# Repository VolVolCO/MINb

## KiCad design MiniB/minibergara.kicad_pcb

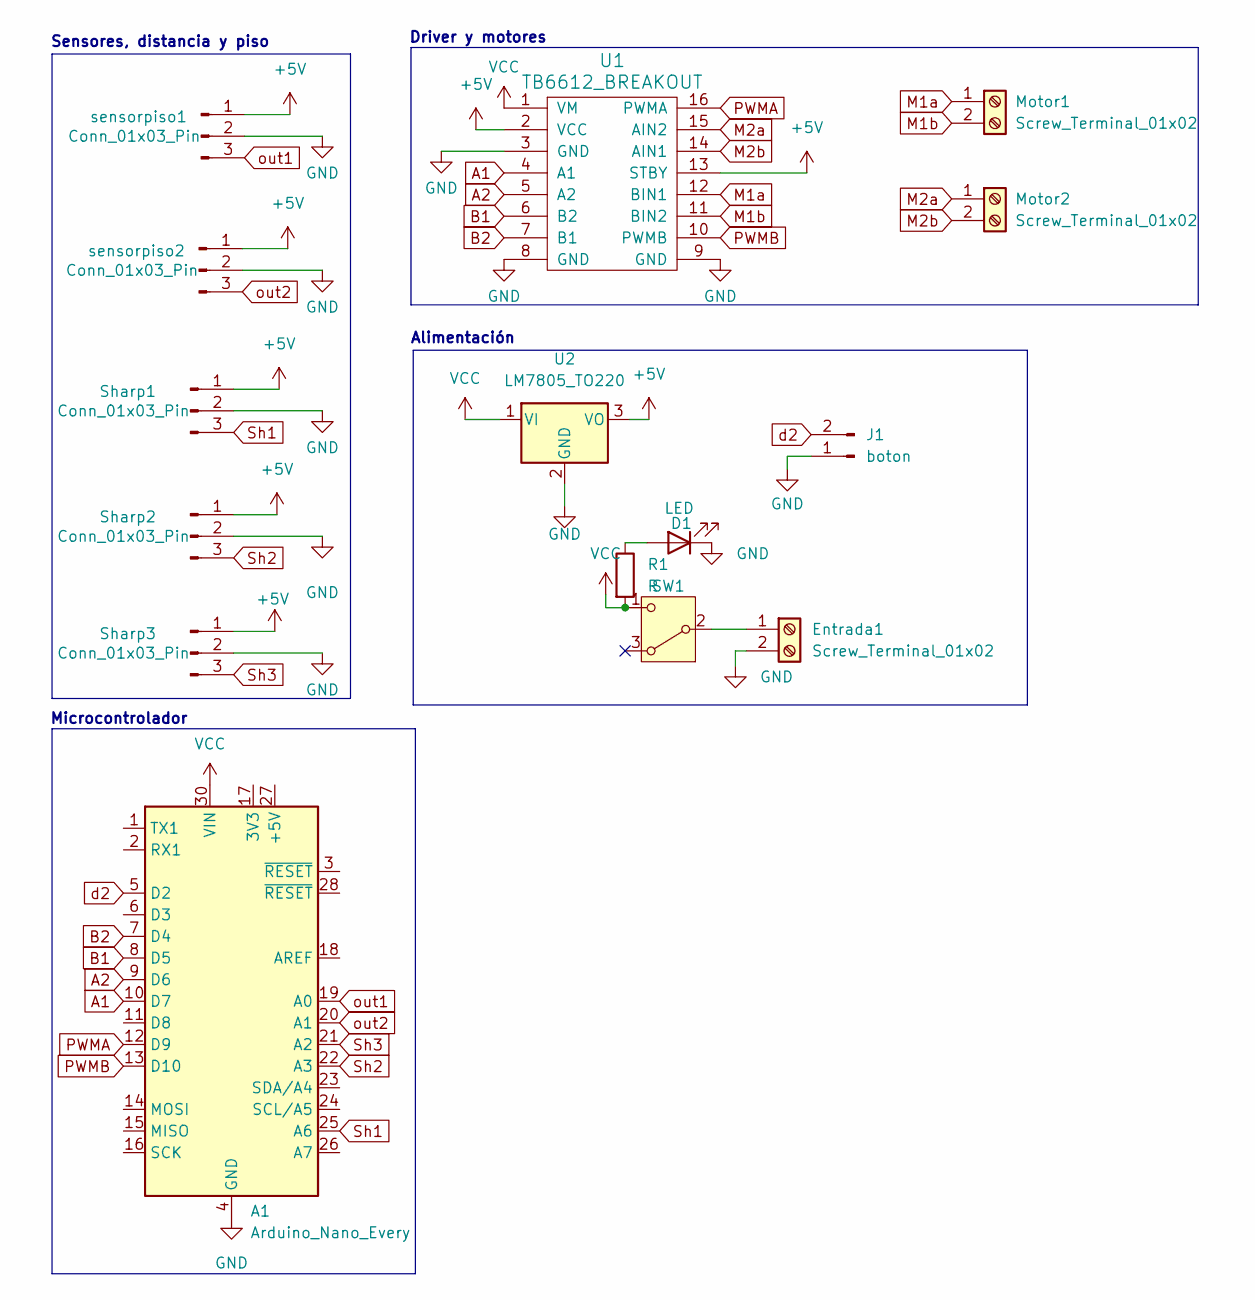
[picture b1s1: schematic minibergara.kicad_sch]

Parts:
A1: Arduino_Nano_Every; Arduino_Nano
D1: LED; LED_0805_2012Metric
Entrada1: Screw_Terminal_01x02; TerminalBlock_MaiXu_MX126-5.0-02P_1x02_P5.00mm
J1: boton; PinHeader_1x02_P2.54mm_Vertical
Motor1, Motor2: Screw_Terminal_01x02; TerminalBlock_MaiXu_MX126-5.0-02P_1x02_P5.00mm
R1: R; R_0805_2012Metric
SW1: SW_Nidec_CAS-120A1; SW_SPDT_TH_Vertical
Sharp1, Sharp2, Sharp3: Conn_01x03_Pin; JST-3V
U1: TB6612_BREAKOUT; TB6612_Breakout
U2: LM7805_TO220; TO-263-3_TabPin2
sensorpiso1, sensorpiso2: Conn_01x03_Pin; JST-3V

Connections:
+5V: Sharp1.1, Sharp2.1, Sharp3.1, U1.2 (VCC), U1.13 (STBY), U2.3 (VO), sensorpiso1.1, sensorpiso2.1
A1: A1.10 (D7), U1.4 (A1)
A2: A1.9 (D6), U1.5 (A2)
B1: A1.8 (D5), U1.6 (B2)
B2: A1.7 (D4), U1.7 (B1)
GND: A1.4 (GND), A1.29 (GND), D1.1 (K), Entrada1.2, J1.1, Sharp1.2, Sharp2.2, Sharp3.2, U1.3 (GND), U1.8 (GND), U1.9 (GND), U2.2 (GND), sensorpiso1.2, sensorpiso2.2
M1a: Motor1.1, U1.12 (BIN1)
M1b: Motor1.2, U1.11 (BIN2)
M2a: Motor2.1, U1.15 (AIN2)
M2b: Motor2.2, U1.14 (AIN1)
unnamed: D1.2 (A), R1.1
unnamed: Entrada1.1, SW1.2 (B)
PWMA: A1.12 (D9), U1.16 (PWMA)
PWMB: A1.13 (D10), U1.10 (PWMB)
Sh1: A1.25 (A6), Sharp1.3
Sh2: A1.22 (A3), Sharp2.3
Sh3: A1.21 (A2), Sharp3.3
VCC: A1.30 (VIN), R1.2, SW1.1 (C), U1.1 (VM), U2.1 (VI)
d2: A1.5 (D2), J1.2
out1: A1.19 (A0), sensorpiso1.3
out2: A1.20 (A1), sensorpiso2.3

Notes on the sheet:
Alimentación
Microcontrolador
Sensores, distancia y piso
Driver y motores

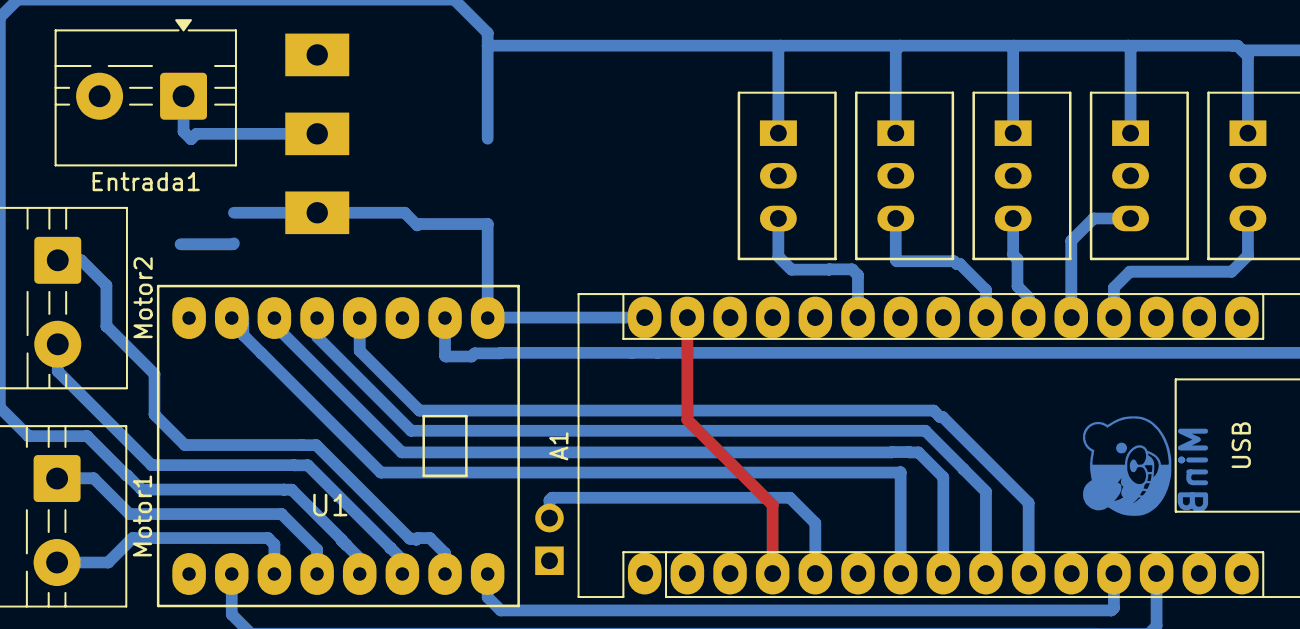
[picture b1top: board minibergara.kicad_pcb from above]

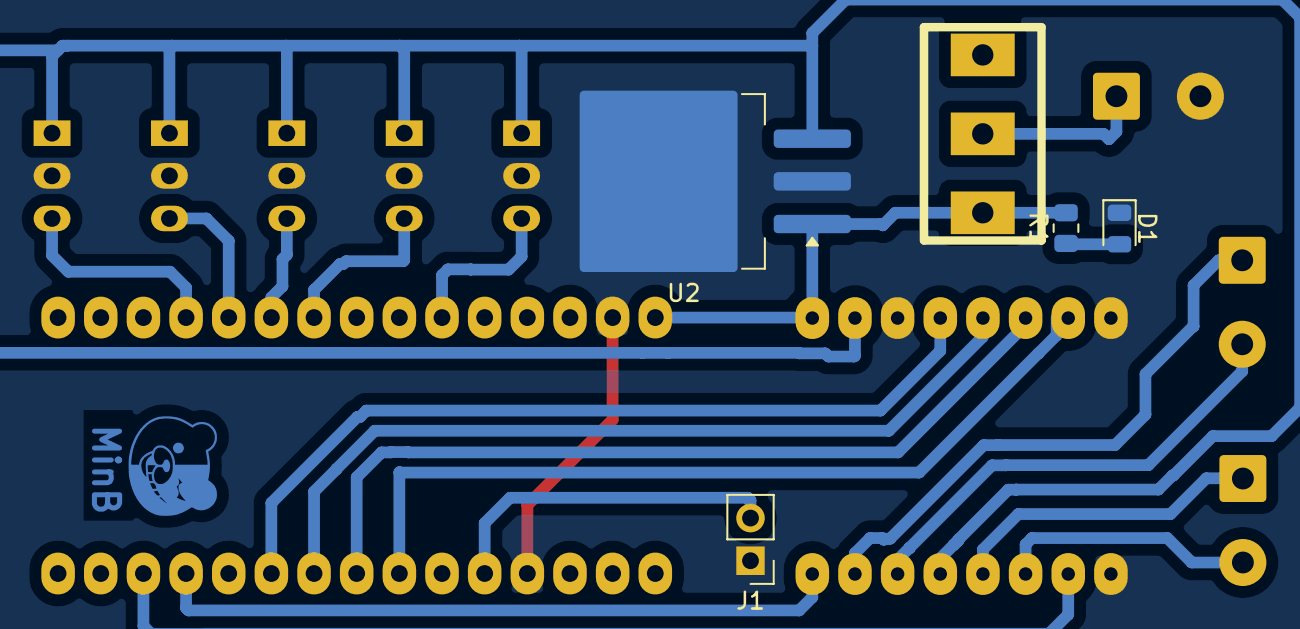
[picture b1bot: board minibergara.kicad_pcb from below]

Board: 2 copper layers, 15 parts (5 on the bottom side), 21 nets.

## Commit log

2025-09-17 MiniBe
    mini sumo with Arduino Nano
2025-09-17 falta mover nano
    move el nano abajo con las pistas
2025-09-23 MinB 23.9.25
    para corregir
2025-09-24 Para corregir 24.9.25
    Asdasdas
2025-09-24 boton y led puestos
    hola
